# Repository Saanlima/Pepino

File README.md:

# Pepino
**For further information see the Pepino [Wiki](http://www.saanlima.com/pepino/index.php?title=Welcome_to_Pepino).**

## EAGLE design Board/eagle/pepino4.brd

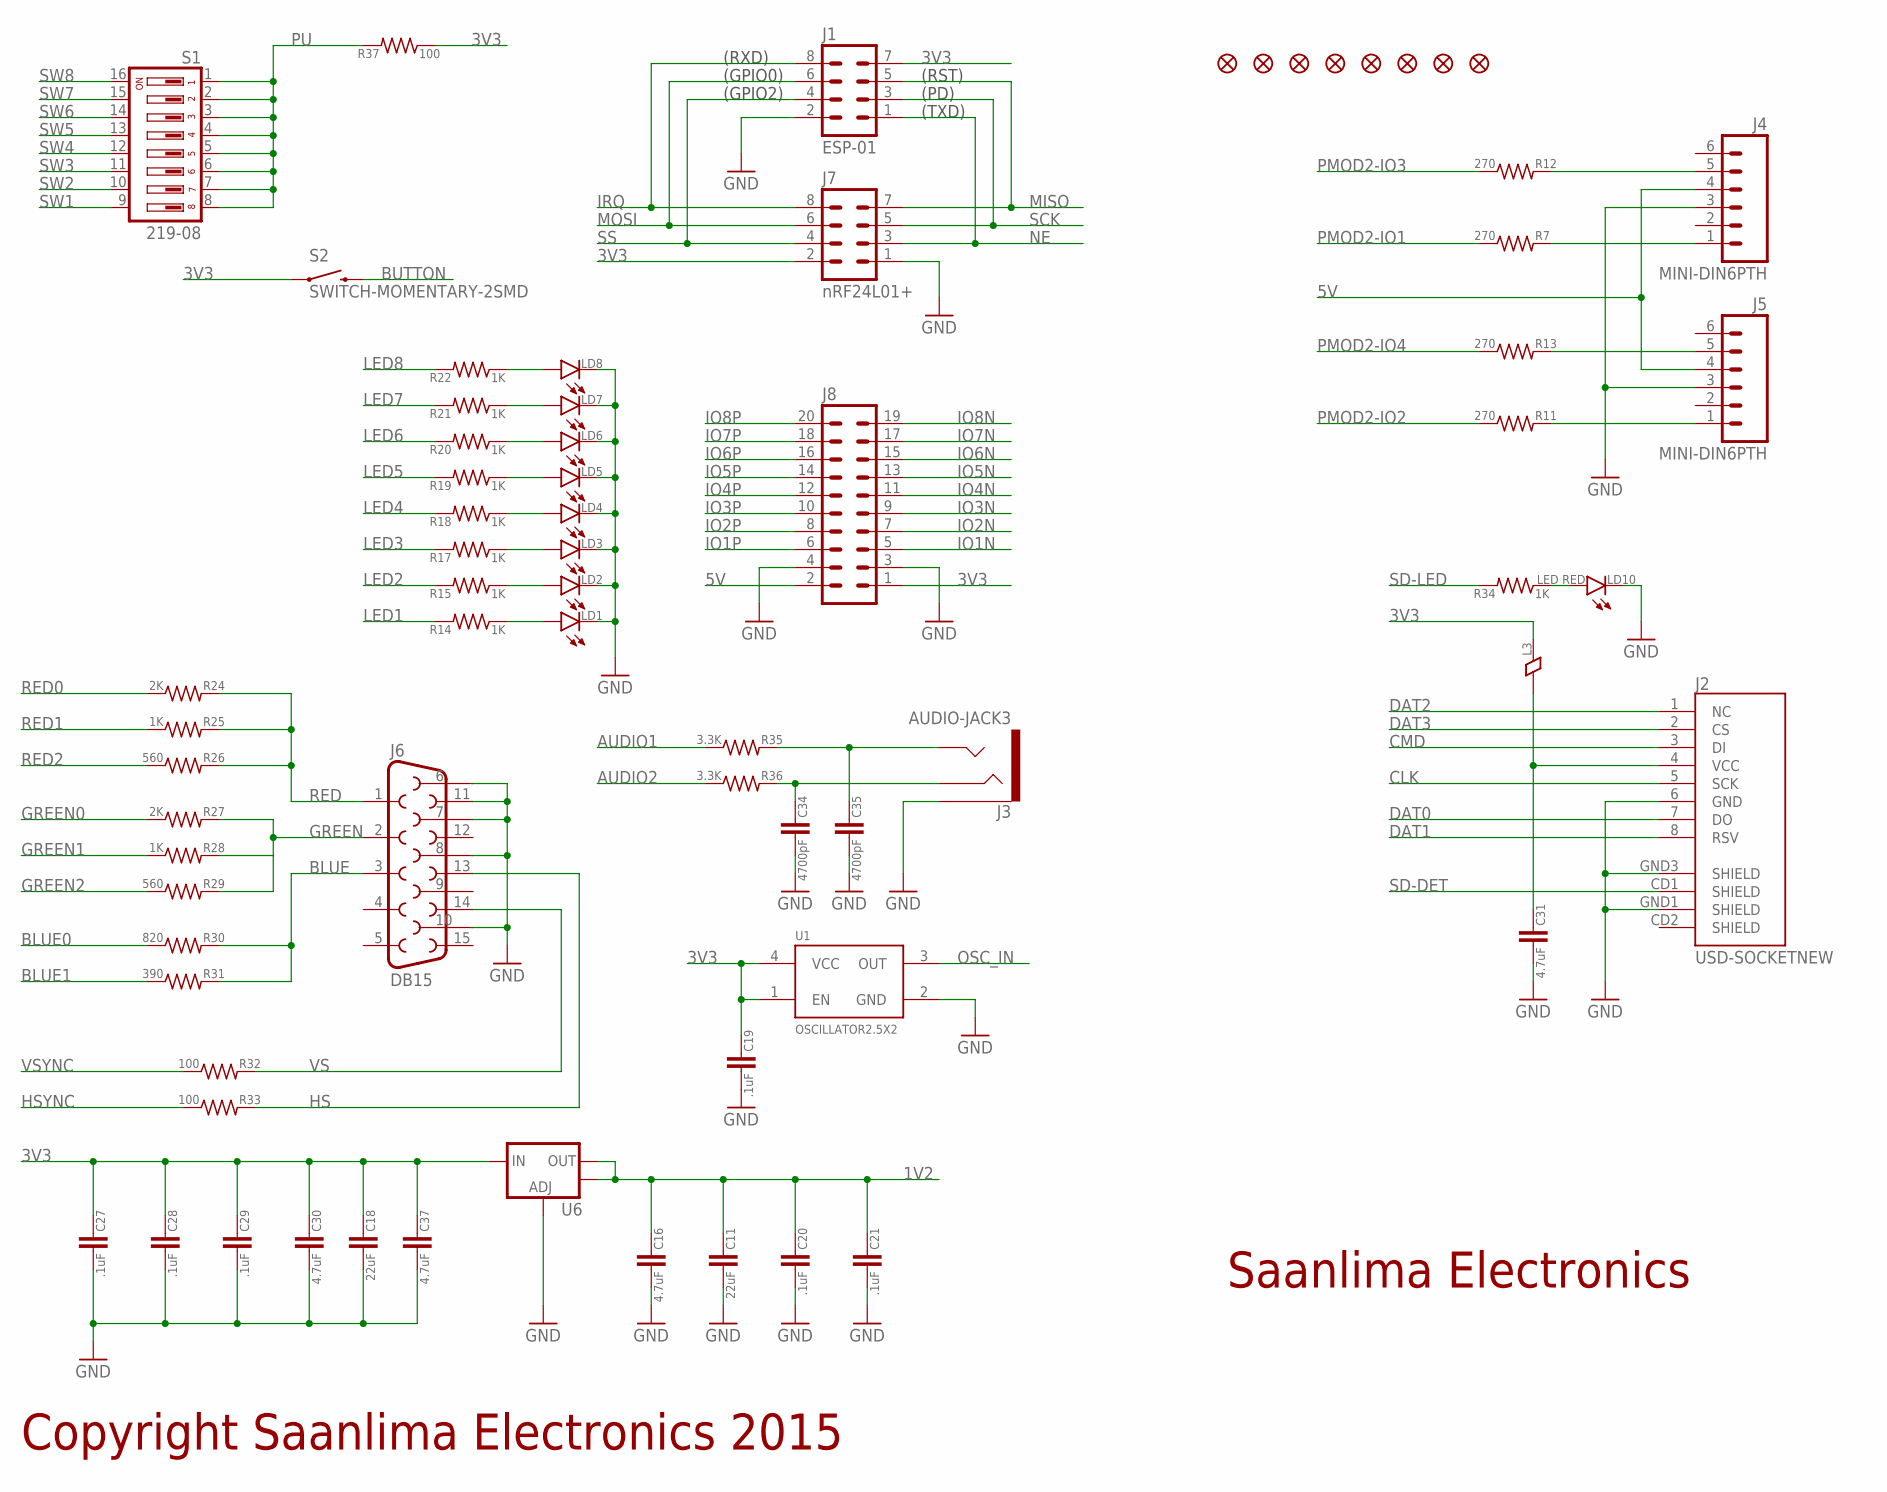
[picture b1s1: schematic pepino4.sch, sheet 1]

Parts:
C11, C18: 22uF; 0805
C16, C30, C31, C37: 4.7uF; 0402
C19, C20, C21, C27, C28, C29: .1uF; 0402
C34, C35: 4700pF; 0402
J1: ESP-01; MA04-2
J2: USD-SOCKETNEW; MICRO-SD-SOCKET-PP
J3: AUDIO-JACK3; AUDIO-JACK-3.5MM-3
J4, J5: MINI-DIN6PTH; MINI-DIN6
J6: DB15
J7: nRF24L01+; MA04-2
J8: MA10-2
JP1, JP2, JP3, JP4, JP5, JP6, JP7, JP8: FIDUCIAL1X2; FIDUCIAL-1X2
L3: FERRITE0402; 0402
LD1, LD2, LD3, LD4, LD5, LD6, LD7, LD8: LED0805; 0805_POL
LD10: LED RED; 0805_POL
R7, R11, R12, R13: 270; 0402
R14, R15, R17, R18, R19, R20, R21, R22, R25, R28, R34: 1K; 0402
R24, R27: 2K; 0402
R26, R29: 560; 0402
R30: 820; 0402
R31: 390; 0402
R32, R33, R37: 100; 0402
R35, R36: 3.3K; 0402
S1: 219-08; CTS-219-08
S2: SWITCH-MOMENTARY-2SMD; TACTILE_SWITCH_SMD
U1: OSCILLATOR2.5X2; CRYSTAL-OSC-SMD-2.5X2
U6: V_REG_LM1117SOT223; SOT223

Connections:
1V2: C11.1, C16.1, C20.1, C21.1, U6.2 (OUT), U6.4 (OUT); also elsewhere on the board
3V3: C18.1, C19.1, C27.1, C28.1, C29.1, C30.1, C37.1, J1.7, J7.2, J8.1, L3.2, R37.1, S2.1, U1.1 (EN), U1.4 (VCC), U6.3 (IN); also elsewhere on the board
5V: J4.4, J5.4, J8.2; also elsewhere on the board
AUDIO1: R35.1; also elsewhere on the board
AUDIO2: R36.1; also elsewhere on the board
BLUE: J6.3, R30.2, R31.2
BLUE0: R30.1; also elsewhere on the board
BLUE1: R31.1; also elsewhere on the board
BUTTON: S2.3 (2); also elsewhere on the board
CLK: J2.5 (SCK); also elsewhere on the board
CMD: J2.3 (DI); also elsewhere on the board
DAT0: J2.7 (DO); also elsewhere on the board
DAT1: J2.8 (RSV); also elsewhere on the board
DAT2: J2.1 (NC); also elsewhere on the board
DAT3: J2.2 (CS); also elsewhere on the board
GND: C11.2, C16.2, C18.2, C19.2, C20.2, C21.2, C27.2, C28.2, C29.2, C30.2, C31.2, C34.2, C35.2, C37.2, J1.2, J2.6 (GND), J2.GND1 (SHIELD), J2.GND3 (SHIELD), J3.SLEEVE, J4.3, J5.3, J6.6, J6.7, J6.8, J6.10, J6.11, J7.1, J8.3, J8.4, LD1.- (C), LD2.- (C), LD3.- (C), LD4.- (C), LD5.- (C), LD6.- (C), LD7.- (C), LD8.- (C), LD10.- (C), U1.2 (GND), U6.1 (ADJ); also elsewhere on the board
GREEN: J6.2, R27.2, R28.2, R29.2
GREEN0: R27.1; also elsewhere on the board
GREEN1: R28.1; also elsewhere on the board
GREEN2: R29.1; also elsewhere on the board
HS: J6.13, R33.2
HSYNC: R33.1; also elsewhere on the board
IO1N: J8.5; also elsewhere on the board
IO1P: J8.6; also elsewhere on the board
IO2N: J8.7; also elsewhere on the board
IO2P: J8.8; also elsewhere on the board
IO3N: J8.9; also elsewhere on the board
IO3P: J8.10; also elsewhere on the board
IO4N: J8.11; also elsewhere on the board
IO4P: J8.12; also elsewhere on the board
IO5N: J8.13; also elsewhere on the board
IO5P: J8.14; also elsewhere on the board
IO6N: J8.15; also elsewhere on the board
IO6P: J8.16; also elsewhere on the board
IO7N: J8.17; also elsewhere on the board
IO7P: J8.18; also elsewhere on the board
IO8N: J8.19; also elsewhere on the board
IO8P: J8.20; also elsewhere on the board
IRQ: J1.8, J7.8; also elsewhere on the board
LED1: R14.2; also elsewhere on the board
LED2: R15.2; also elsewhere on the board
LED3: R17.2; also elsewhere on the board
LED4: R18.2; also elsewhere on the board
LED5: R19.2; also elsewhere on the board
LED6: R20.2; also elsewhere on the board
LED7: R21.2; also elsewhere on the board
LED8: R22.2; also elsewhere on the board
MISO: J1.5, J7.7; also elsewhere on the board
MOSI: J1.6, J7.6; also elsewhere on the board
unnamed: J4.1, R7.2
unnamed: J5.1, R11.2
unnamed: J4.5, R12.2
unnamed: C31.1, J2.4 (VCC), L3.1
unnamed: J5.5, R13.2
unnamed: LD1.+ (A), R14.1
unnamed: LD7.+ (A), R21.1
unnamed: LD2.+ (A), R15.1
unnamed: LD3.+ (A), R17.1
unnamed: LD4.+ (A), R18.1
unnamed: LD5.+ (A), R19.1
unnamed: LD6.+ (A), R20.1
unnamed: LD8.+ (A), R22.1
unnamed: LD10.+ (A), R34.1
unnamed: C34.1, J3.RING, R36.2
unnamed: C35.1, J3.TIP, R35.2
NE: J1.1, J7.3; also elsewhere on the board
OSC_IN: U1.3 (OUT); also elsewhere on the board
PMOD2-IO1: R7.1; also elsewhere on the board
PMOD2-IO2: R11.1; also elsewhere on the board
PMOD2-IO3: R12.1; also elsewhere on the board
PMOD2-IO4: R13.1; also elsewhere on the board
PU: R37.2, S1.1, S1.2, S1.3, S1.4, S1.5, S1.6, S1.7, S1.8
RED: J6.1, R24.2, R25.2, R26.2
RED0: R24.1; also elsewhere on the board
RED1: R25.1; also elsewhere on the board
RED2: R26.1; also elsewhere on the board
SCK: J1.3, J7.5; also elsewhere on the board
SD-DET: J2.CD1 (SHIELD); also elsewhere on the board
SD-LED: R34.2; also elsewhere on the board
SS: J1.4, J7.4; also elsewhere on the board
SW1: S1.9; also elsewhere on the board
SW2: S1.10; also elsewhere on the board
SW3: S1.11; also elsewhere on the board
SW4: S1.12; also elsewhere on the board
SW5: S1.13; also elsewhere on the board
SW6: S1.14; also elsewhere on the board
SW7: S1.15; also elsewhere on the board
SW8: S1.16; also elsewhere on the board
VS: J6.14, R32.2
VSYNC: R32.1; also elsewhere on the board

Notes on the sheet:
(RST)
(PD)
(TXD)
(RXD)
(GPIO0)
(GPIO2)
Saanlima Electronics
Copyright Saanlima Electronics 2015

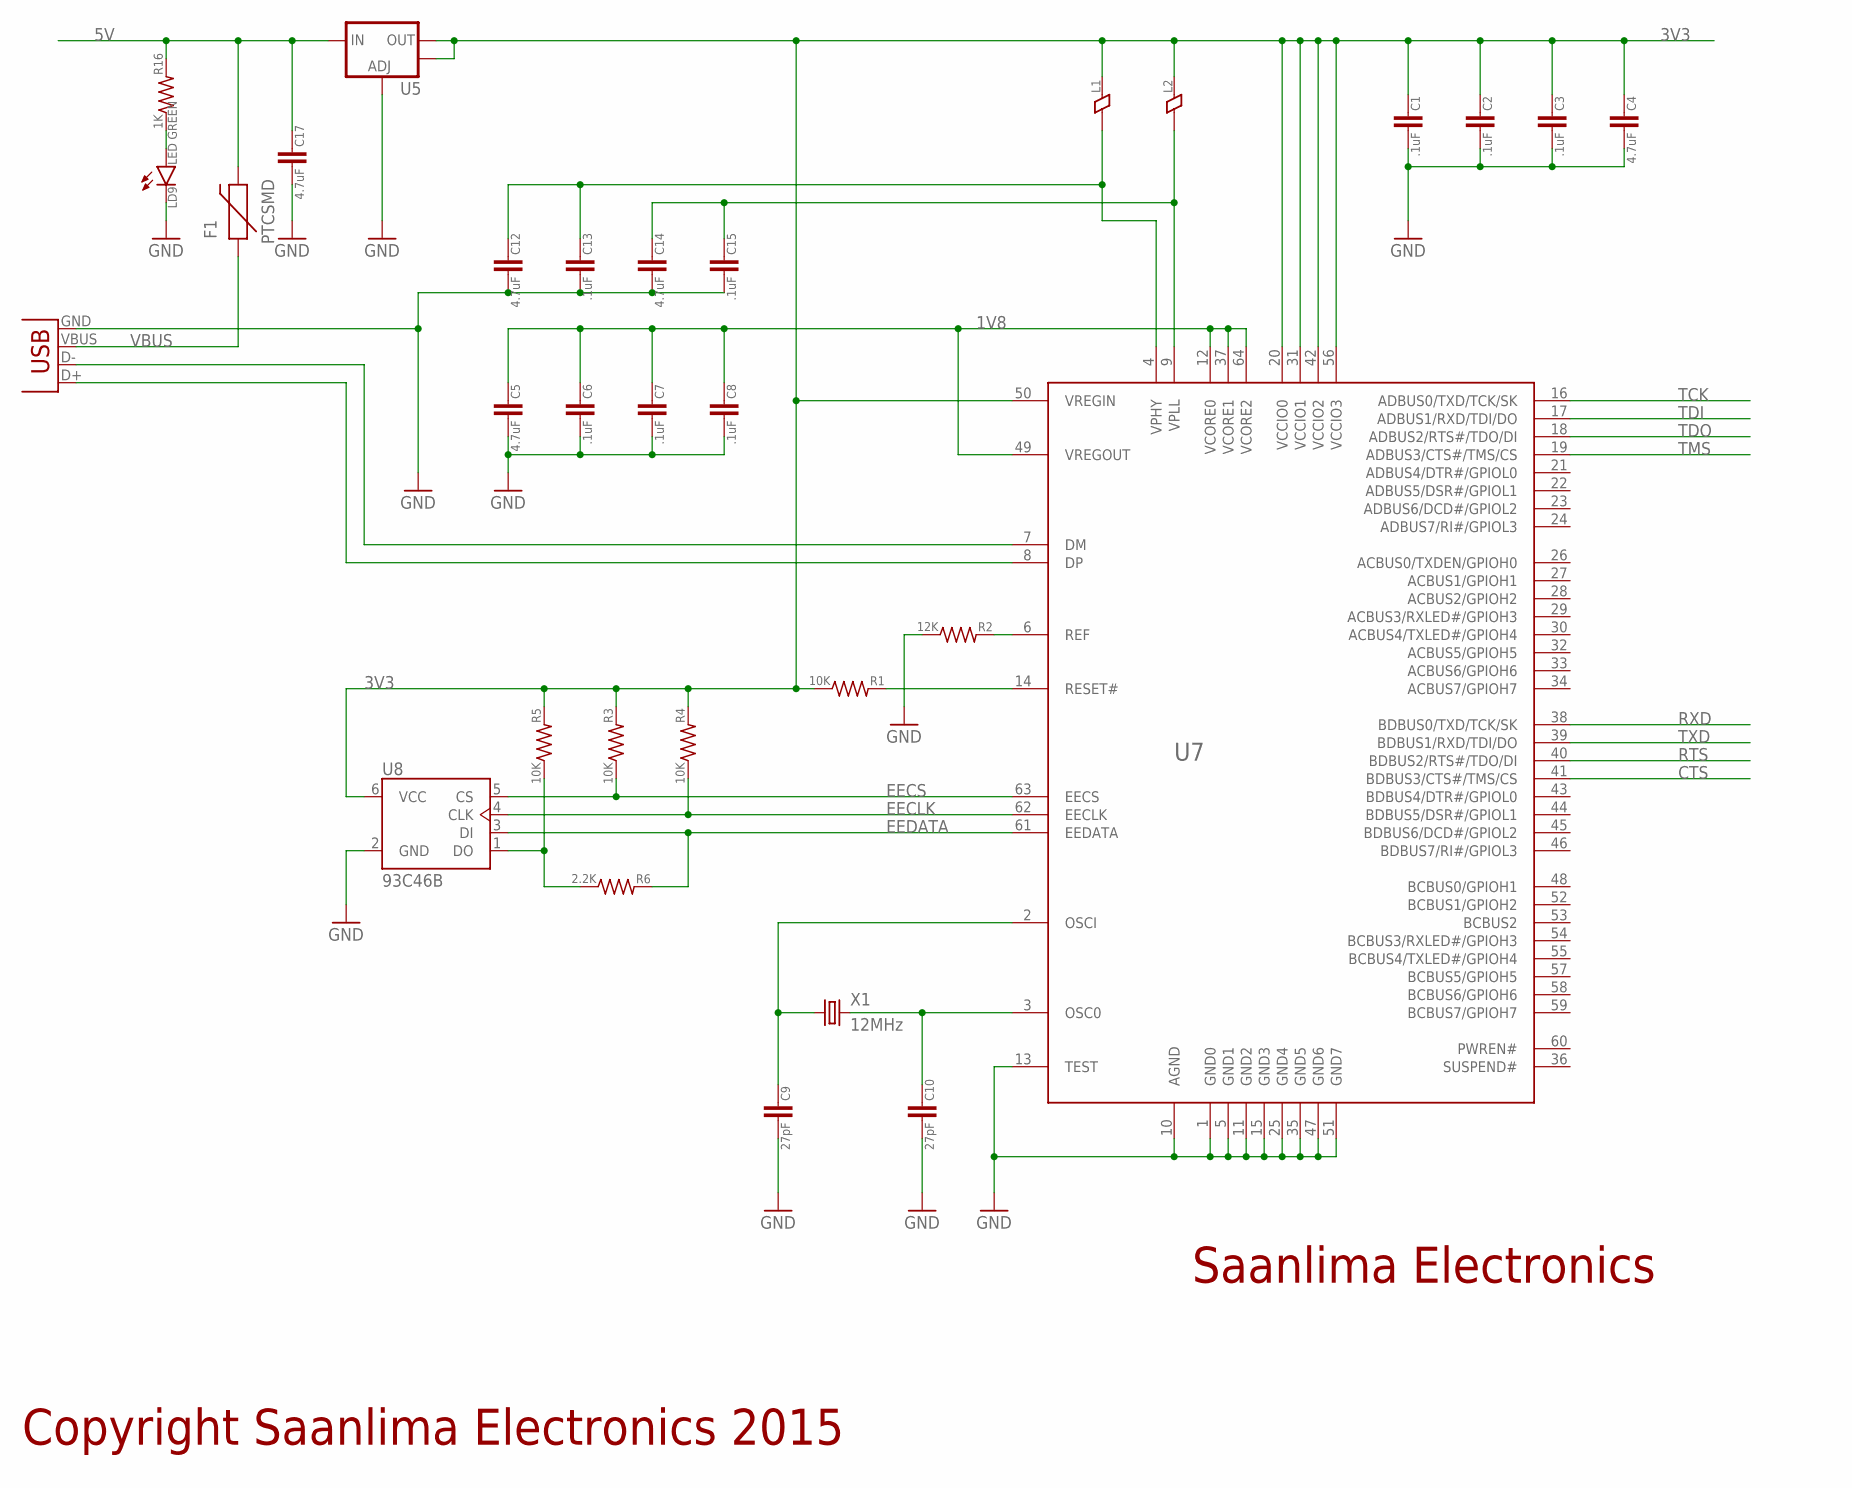
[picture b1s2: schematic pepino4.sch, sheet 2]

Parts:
C1, C2, C3, C6, C7, C8, C13, C15: .1uF; 0402
C4, C5, C12, C14: 4.7uF; 0402
C9, C10: 27pF; 0402
C17: 4.7uF; 0603
F1: PTCSMD; PTC-1206
J9: USBSMD; USB-MINIB
L1, L2: FERRITE0402; 0402
LD9: LED GREEN; 0805_POL
R1, R3, R4, R5: 10K; 0402
R2: 12K; 0402
R6: 2.2K; 0402
R16: 1K; 0402
U5: V_REG_LM1117SOT223; SOT223
U7: DP-EAGLELIBRARY_FT2232H; DP-EAGLELIBRARY_LQFP64
U8: 93C46B; SOT23-6
X1: 12MHz; CRYSTAL3.2X2.5MM

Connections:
1V8: C5.1, C6.1, C7.1, C8.1, U7.12 (VCORE0), U7.37 (VCORE1), U7.49 (VREGOUT), U7.64 (VCORE2)
3V3: C1.1, C2.1, C3.1, C4.1, L1.2, L2.2, R1.1, R3.2, R4.2, R5.2, U5.2 (OUT), U5.4 (OUT), U7.20 (VCCIO0), U7.31 (VCCIO1), U7.42 (VCCIO2), U7.50 (VREGIN), U7.56 (VCCIO3), U8.6 (VCC); also elsewhere on the board
5V: C17.1, F1.2, R16.2, U5.3 (IN); also elsewhere on the board
CTS: U7.41 (BDBUS3/CTS#/TMS/CS); also elsewhere on the board
EECLK: R4.1, U7.62 (EECLK), U8.4 (CLK)
EECS: R3.1, U7.63 (EECS), U8.5 (CS)
EEDATA: R6.2, U7.61 (EEDATA), U8.3 (DI)
GND: C1.2, C2.2, C3.2, C4.2, C5.2, C6.2, C7.2, C8.2, C9.2, C10.2, C12.2, C13.2, C14.2, C15.2, C17.2, J9.GND, LD9.- (C), R2.1, U5.1 (ADJ), U7.1 (GND0), U7.5 (GND1), U7.10 (AGND), U7.11 (GND2), U7.13 (TEST), U7.15 (GND3), U7.25 (GND4), U7.35 (GND5), U7.47 (GND6), U7.51 (GND7), U8.2 (GND); also elsewhere on the board
unnamed: C9.1, U7.2 (OSCI), X1.1
unnamed: C10.1, U7.3 (OSC0), X1.3 (2)
unnamed: LD9.+ (A), R16.1
unnamed: J9.D-, U7.7 (DM)
unnamed: J9.D+, U7.8 (DP)
unnamed: C14.1, C15.1, L2.1, U7.9 (VPLL)
unnamed: R1.2, U7.14 (RESET#)
unnamed: R2.2, U7.6 (REF)
unnamed: C12.1, C13.1, L1.1, U7.4 (VPHY)
unnamed: R5.1, R6.1, U8.1 (DO)
RTS: U7.40 (BDBUS2/RTS#/TDO/DI); also elsewhere on the board
RXD: U7.38 (BDBUS0/TXD/TCK/SK); also elsewhere on the board
TCK: U7.16 (ADBUS0/TXD/TCK/SK); also elsewhere on the board
TDI: U7.17 (ADBUS1/RXD/TDI/DO); also elsewhere on the board
TDO: U7.18 (ADBUS2/RTS#/TDO/DI); also elsewhere on the board
TMS: U7.19 (ADBUS3/CTS#/TMS/CS); also elsewhere on the board
TXD: U7.39 (BDBUS1/RXD/TDI/DO); also elsewhere on the board
VBUS: F1.1, J9.VBUS

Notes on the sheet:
Copyright Saanlima Electronics 2015
Saanlima Electronics

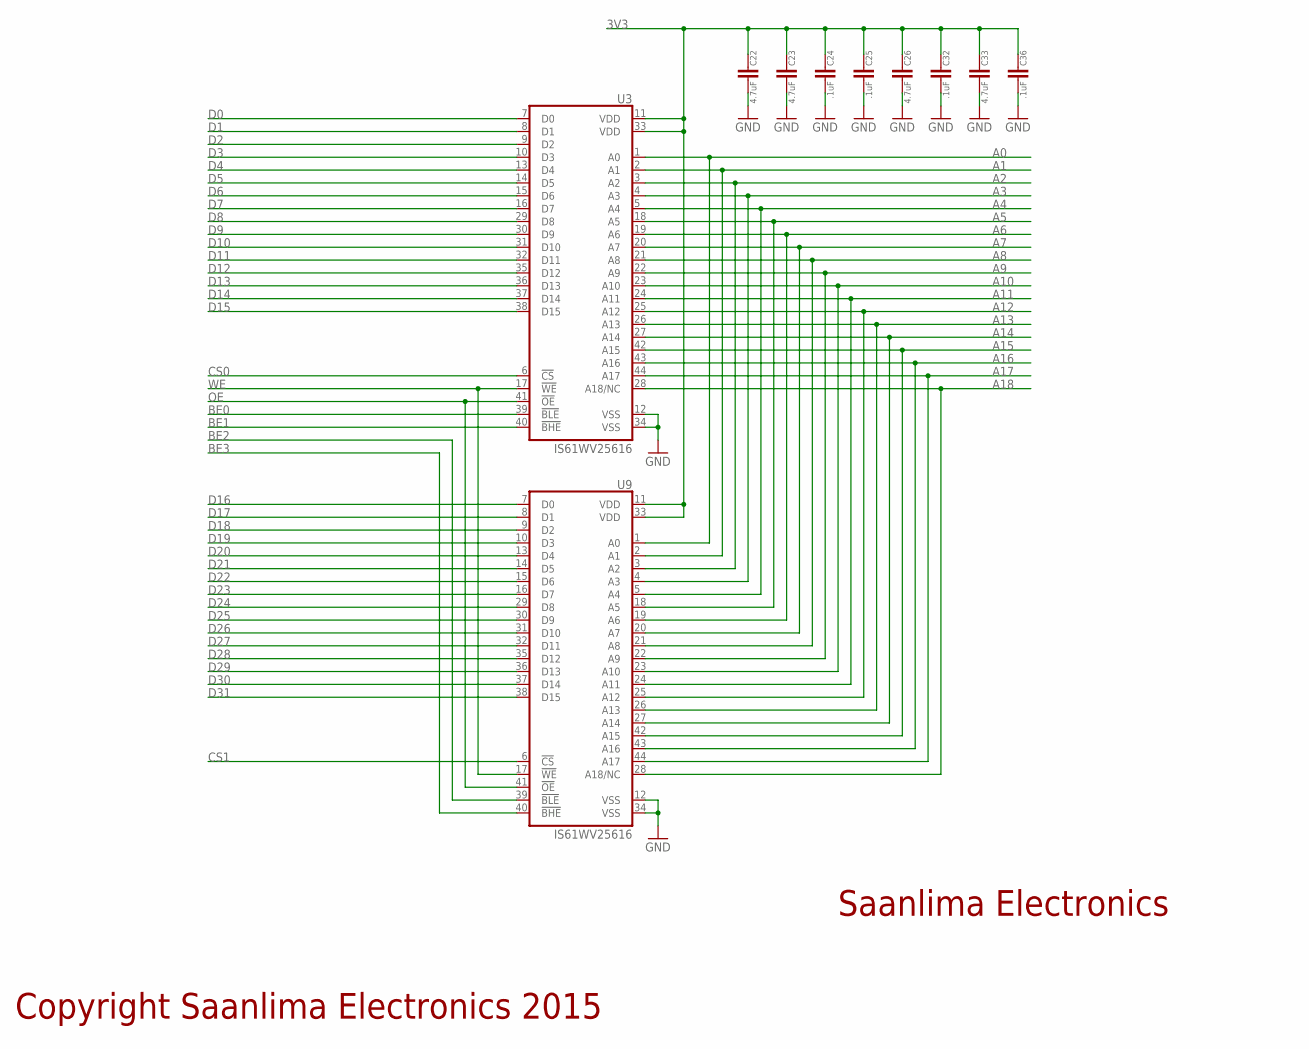
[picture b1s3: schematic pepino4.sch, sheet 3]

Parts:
C22, C23, C26, C33: 4.7uF; 0402
C24, C25, C32, C36: .1uF; 0402
U3, U9: IS61WV25616; TSOP44-II

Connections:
3V3: C22.1, C23.1, C24.1, C25.1, C26.1, C32.1, C33.1, C36.1, U3.11 (VDD), U3.33 (VDD), U9.11 (VDD), U9.33 (VDD); also elsewhere on the board
A0: U3.1 (A0), U9.1 (A0); also elsewhere on the board
A1: U3.2 (A1), U9.2 (A1); also elsewhere on the board
A2: U3.3 (A2), U9.3 (A2); also elsewhere on the board
A3: U3.4 (A3), U9.4 (A3); also elsewhere on the board
A4: U3.5 (A4), U9.5 (A4); also elsewhere on the board
A5: U3.18 (A5), U9.18 (A5); also elsewhere on the board
A6: U3.19 (A6), U9.19 (A6); also elsewhere on the board
A7: U3.20 (A7), U9.20 (A7); also elsewhere on the board
A8: U3.21 (A8), U9.21 (A8); also elsewhere on the board
A9: U3.22 (A9), U9.22 (A9); also elsewhere on the board
A10: U3.23 (A10), U9.23 (A10); also elsewhere on the board
A11: U3.24 (A11), U9.24 (A11); also elsewhere on the board
A12: U3.25 (A12), U9.25 (A12); also elsewhere on the board
A13: U3.26 (A13), U9.26 (A13); also elsewhere on the board
A14: U3.27 (A14), U9.27 (A14); also elsewhere on the board
A15: U3.42 (A15), U9.42 (A15); also elsewhere on the board
A16: U3.43 (A16), U9.43 (A16); also elsewhere on the board
A17: U3.44 (A17), U9.44 (A17); also elsewhere on the board
A18: U3.28 (A18/NC), U9.28 (A18/NC); also elsewhere on the board
BE0: U3.39 (!BLE); also elsewhere on the board
BE1: U3.40 (!BHE); also elsewhere on the board
BE2: U9.39 (!BLE); also elsewhere on the board
BE3: U9.40 (!BHE); also elsewhere on the board
CS0: U3.6 (!CS); also elsewhere on the board
CS1: U9.6 (!CS); also elsewhere on the board
D0: U3.7 (D0); also elsewhere on the board
D1: U3.8 (D1); also elsewhere on the board
D2: U3.9 (D2); also elsewhere on the board
D3: U3.10 (D3); also elsewhere on the board
D4: U3.13 (D4); also elsewhere on the board
D5: U3.14 (D5); also elsewhere on the board
D6: U3.15 (D6); also elsewhere on the board
D7: U3.16 (D7); also elsewhere on the board
D8: U3.29 (D8); also elsewhere on the board
D9: U3.30 (D9); also elsewhere on the board
D10: U3.31 (D10); also elsewhere on the board
D11: U3.32 (D11); also elsewhere on the board
D12: U3.35 (D12); also elsewhere on the board
D13: U3.36 (D13); also elsewhere on the board
D14: U3.37 (D14); also elsewhere on the board
D15: U3.38 (D15); also elsewhere on the board
D16: U9.7 (D0); also elsewhere on the board
D17: U9.8 (D1); also elsewhere on the board
D18: U9.9 (D2); also elsewhere on the board
D19: U9.10 (D3); also elsewhere on the board
D20: U9.13 (D4); also elsewhere on the board
D21: U9.14 (D5); also elsewhere on the board
D22: U9.15 (D6); also elsewhere on the board
D23: U9.16 (D7); also elsewhere on the board
D24: U9.29 (D8); also elsewhere on the board
D25: U9.30 (D9); also elsewhere on the board
D26: U9.31 (D10); also elsewhere on the board
D27: U9.32 (D11); also elsewhere on the board
D28: U9.35 (D12); also elsewhere on the board
D29: U9.36 (D13); also elsewhere on the board
D30: U9.37 (D14); also elsewhere on the board
D31: U9.38 (D15); also elsewhere on the board
GND: C22.2, C23.2, C24.2, C25.2, C26.2, C32.2, C33.2, C36.2, U3.12 (VSS), U3.34 (VSS), U9.12 (VSS), U9.34 (VSS); also elsewhere on the board
OE: U3.41 (!OE), U9.41 (!OE); also elsewhere on the board
WE: U3.17 (!WE), U9.17 (!WE); also elsewhere on the board

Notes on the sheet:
Copyright Saanlima Electronics 2015
Saanlima Electronics

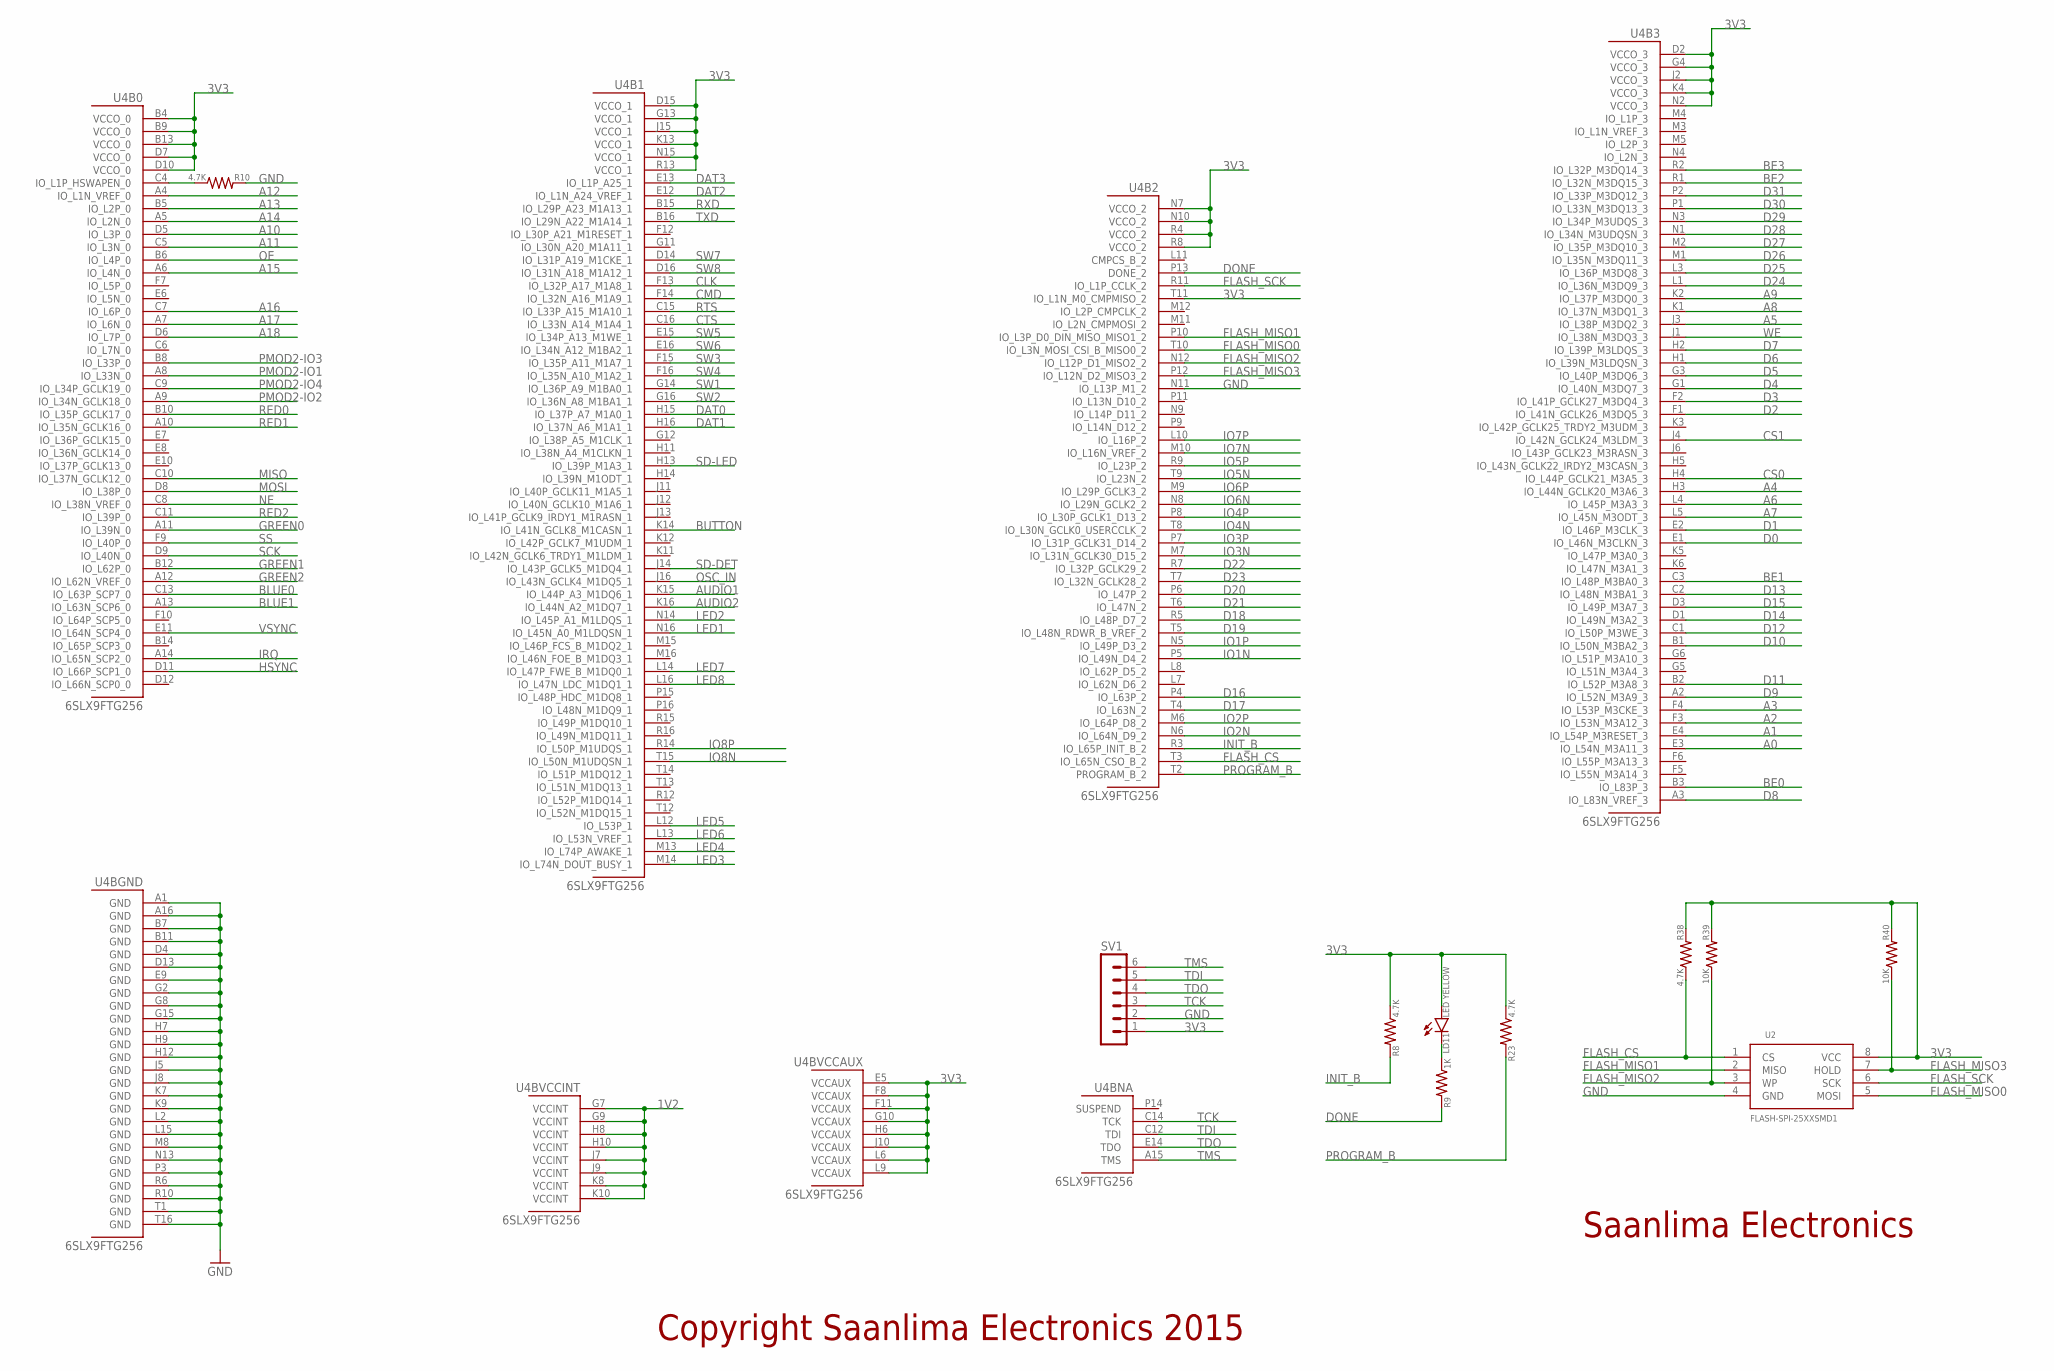
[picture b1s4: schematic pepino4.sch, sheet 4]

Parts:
LD11: LED YELLOW; 0805_POL
R8, R10, R23, R38: 4.7K; 0402
R9: 1K; 0402
R39, R40: 10K; 0402
SV1: MA06-1
U2: FLASH-SPI-25XXSMD1; SO08-EIAJ
U4: 6SLX9FTG256; FT256

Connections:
1V2: U4.G7 (VCCINT), U4.G9 (VCCINT), U4.H8 (VCCINT), U4.H10 (VCCINT), U4.J7 (VCCINT), U4.J9 (VCCINT), U4.K8 (VCCINT), U4.K10 (VCCINT); also elsewhere on the board
3V3: LD11.+ (A), R8.1, R23.1, R38.2, R39.2, R40.2, SV1.1, U2.8 (VCC), U4.B4 (VCCO_0), U4.B9 (VCCO_0), U4.B13 (VCCO_0), U4.D2 (VCCO_3), U4.D7 (VCCO_0), U4.D10 (VCCO_0), U4.D15 (VCCO_1), U4.E5 (VCCAUX), U4.F8 (VCCAUX), U4.F11 (VCCAUX), U4.G4 (VCCO_3), U4.G10 (VCCAUX), U4.G13 (VCCO_1), U4.H6 (VCCAUX), U4.J2 (VCCO_3), U4.J10 (VCCAUX), U4.J15 (VCCO_1), U4.K4 (VCCO_3), U4.K13 (VCCO_1), U4.L6 (VCCAUX), U4.L9 (VCCAUX), U4.N2 (VCCO_3), U4.N7 (VCCO_2), U4.N10 (VCCO_2), U4.N15 (VCCO_1), U4.R4 (VCCO_2), U4.R8 (VCCO_2), U4.R13 (VCCO_1), U4.T11 (IO_L1N_M0_CMPMISO_2); also elsewhere on the board
A0: U4.E3 (IO_L54N_M3A11_3); also elsewhere on the board
A1: U4.E4 (IO_L54P_M3RESET_3); also elsewhere on the board
A2: U4.F3 (IO_L53N_M3A12_3); also elsewhere on the board
A3: U4.F4 (IO_L53P_M3CKE_3); also elsewhere on the board
A4: U4.H3 (IO_L44N_GCLK20_M3A6_3); also elsewhere on the board
A5: U4.J3 (IO_L38P_M3DQ2_3); also elsewhere on the board
A6: U4.L4 (IO_L45P_M3A3_3); also elsewhere on the board
A7: U4.L5 (IO_L45N_M3ODT_3); also elsewhere on the board
A8: U4.K1 (IO_L37N_M3DQ1_3); also elsewhere on the board
A9: U4.K2 (IO_L37P_M3DQ0_3); also elsewhere on the board
A10: U4.D5 (IO_L3P_0); also elsewhere on the board
A11: U4.C5 (IO_L3N_0); also elsewhere on the board
A12: U4.A4 (IO_L1N_VREF_0); also elsewhere on the board
A13: U4.B5 (IO_L2P_0); also elsewhere on the board
A14: U4.A5 (IO_L2N_0); also elsewhere on the board
A15: U4.A6 (IO_L4N_0); also elsewhere on the board
A16: U4.C7 (IO_L6P_0); also elsewhere on the board
A17: U4.A7 (IO_L6N_0); also elsewhere on the board
A18: U4.D6 (IO_L7P_0); also elsewhere on the board
AUDIO1: U4.K15 (IO_L44P_A3_M1DQ6_1); also elsewhere on the board
AUDIO2: U4.K16 (IO_L44N_A2_M1DQ7_1); also elsewhere on the board
BE0: U4.B3 (IO_L83P_3); also elsewhere on the board
BE1: U4.C3 (IO_L48P_M3BA0_3); also elsewhere on the board
BE2: U4.R1 (IO_L32N_M3DQ15_3); also elsewhere on the board
BE3: U4.R2 (IO_L32P_M3DQ14_3); also elsewhere on the board
BLUE0: U4.C13 (IO_L63P_SCP7_0); also elsewhere on the board
BLUE1: U4.A13 (IO_L63N_SCP6_0); also elsewhere on the board
BUTTON: U4.K14 (IO_L41N_GCLK8_M1CASN_1); also elsewhere on the board
CLK: U4.F13 (IO_L32P_A17_M1A8_1); also elsewhere on the board
CMD: U4.F14 (IO_L32N_A16_M1A9_1); also elsewhere on the board
CS0: U4.H4 (IO_L44P_GCLK21_M3A5_3); also elsewhere on the board
CS1: U4.J4 (IO_L42N_GCLK24_M3LDM_3); also elsewhere on the board
CTS: U4.C16 (IO_L33N_A14_M1A4_1); also elsewhere on the board
D0: U4.E1 (IO_L46N_M3CLKN_3); also elsewhere on the board
D1: U4.E2 (IO_L46P_M3CLK_3); also elsewhere on the board
D2: U4.F1 (IO_L41N_GCLK26_M3DQ5_3); also elsewhere on the board
D3: U4.F2 (IO_L41P_GCLK27_M3DQ4_3); also elsewhere on the board
D4: U4.G1 (IO_L40N_M3DQ7_3); also elsewhere on the board
D5: U4.G3 (IO_L40P_M3DQ6_3); also elsewhere on the board
D6: U4.H1 (IO_L39N_M3LDQSN_3); also elsewhere on the board
D7: U4.H2 (IO_L39P_M3LDQS_3); also elsewhere on the board
D8: U4.A3 (IO_L83N_VREF_3); also elsewhere on the board
D9: U4.A2 (IO_L52N_M3A9_3); also elsewhere on the board
D10: U4.B1 (IO_L50N_M3BA2_3); also elsewhere on the board
D11: U4.B2 (IO_L52P_M3A8_3); also elsewhere on the board
D12: U4.C1 (IO_L50P_M3WE_3); also elsewhere on the board
D13: U4.C2 (IO_L48N_M3BA1_3); also elsewhere on the board
D14: U4.D1 (IO_L49N_M3A2_3); also elsewhere on the board
D15: U4.D3 (IO_L49P_M3A7_3); also elsewhere on the board
D16: U4.P4 (IO_L63P_2); also elsewhere on the board
D17: U4.T4 (IO_L63N_2); also elsewhere on the board
D18: U4.R5 (IO_L48P_D7_2); also elsewhere on the board
D19: U4.T5 (IO_L48N_RDWR_B_VREF_2); also elsewhere on the board
D20: U4.P6 (IO_L47P_2); also elsewhere on the board
D21: U4.T6 (IO_L47N_2); also elsewhere on the board
D22: U4.R7 (IO_L32P_GCLK29_2); also elsewhere on the board
D23: U4.T7 (IO_L32N_GCLK28_2); also elsewhere on the board
D24: U4.L1 (IO_L36N_M3DQ9_3); also elsewhere on the board
D25: U4.L3 (IO_L36P_M3DQ8_3); also elsewhere on the board
D26: U4.M1 (IO_L35N_M3DQ11_3); also elsewhere on the board
D27: U4.M2 (IO_L35P_M3DQ10_3); also elsewhere on the board
D28: U4.N1 (IO_L34N_M3UDQSN_3); also elsewhere on the board
D29: U4.N3 (IO_L34P_M3UDQS_3); also elsewhere on the board
D30: U4.P1 (IO_L33N_M3DQ13_3); also elsewhere on the board
D31: U4.P2 (IO_L33P_M3DQ12_3); also elsewhere on the board
DAT0: U4.H15 (IO_L37P_A7_M1A0_1); also elsewhere on the board
DAT1: U4.H16 (IO_L37N_A6_M1A1_1); also elsewhere on the board
DAT2: U4.E12 (IO_L1N_A24_VREF_1); also elsewhere on the board
DAT3: U4.E13 (IO_L1P_A25_1); also elsewhere on the board
DONE: R9.2, U4.P13 (DONE_2)
FLASH_CS: R38.1, U2.1 (CS), U4.T3 (IO_L65N_CSO_B_2)
FLASH_MISO0: U2.5 (MOSI), U4.T10 (IO_L3N_MOSI_CSI_B_MISO0_2)
FLASH_MISO1: U2.2 (MISO), U4.P10 (IO_L3P_D0_DIN_MISO_MISO1_2)
FLASH_MISO2: R39.1, U2.3 (WP), U4.N12 (IO_L12P_D1_MISO2_2)
FLASH_MISO3: R40.1, U2.7 (HOLD), U4.P12 (IO_L12N_D2_MISO3_2)
FLASH_SCK: U2.6 (SCK), U4.R11 (IO_L1P_CCLK_2)
GND: R10.2, SV1.2, U2.4 (GND), U4.A1 (GND), U4.A16 (GND), U4.B7 (GND), U4.B11 (GND), U4.D4 (GND), U4.D13 (GND), U4.E9 (GND), U4.G2 (GND), U4.G8 (GND), U4.G15 (GND), U4.H7 (GND), U4.H9 (GND), U4.H12 (GND), U4.J5 (GND), U4.J8 (GND), U4.K7 (GND), U4.K9 (GND), U4.L2 (GND), U4.L15 (GND), U4.M8 (GND), U4.N11 (IO_L13P_M1_2), U4.N13 (GND), U4.P3 (GND), U4.R6 (GND), U4.R10 (GND), U4.T1 (GND), U4.T16 (GND); also elsewhere on the board
GREEN0: U4.A11 (IO_L39N_0); also elsewhere on the board
GREEN1: U4.B12 (IO_L62P_0); also elsewhere on the board
GREEN2: U4.A12 (IO_L62N_VREF_0); also elsewhere on the board
HSYNC: U4.D11 (IO_L66P_SCP1_0); also elsewhere on the board
INIT_B: R8.2, U4.R3 (IO_L65P_INIT_B_2)
IO1N: U4.P5 (IO_L49N_D4_2); also elsewhere on the board
IO1P: U4.N5 (IO_L49P_D3_2); also elsewhere on the board
IO2N: U4.N6 (IO_L64N_D9_2); also elsewhere on the board
IO2P: U4.M6 (IO_L64P_D8_2); also elsewhere on the board
IO3N: U4.M7 (IO_L31N_GCLK30_D15_2); also elsewhere on the board
IO3P: U4.P7 (IO_L31P_GCLK31_D14_2); also elsewhere on the board
IO4N: U4.T8 (IO_L30N_GCLK0_USERCCLK_2); also elsewhere on the board
IO4P: U4.P8 (IO_L30P_GCLK1_D13_2); also elsewhere on the board
IO5N: U4.T9 (IO_L23N_2); also elsewhere on the board
IO5P: U4.R9 (IO_L23P_2); also elsewhere on the board
IO6N: U4.N8 (IO_L29N_GCLK2_2); also elsewhere on the board
IO6P: U4.M9 (IO_L29P_GCLK3_2); also elsewhere on the board
IO7N: U4.M10 (IO_L16N_VREF_2); also elsewhere on the board
IO7P: U4.L10 (IO_L16P_2); also elsewhere on the board
IO8N: U4.T15 (IO_L50N_M1UDQSN_1); also elsewhere on the board
IO8P: U4.R14 (IO_L50P_M1UDQS_1); also elsewhere on the board
IRQ: U4.A14 (IO_L65N_SCP2_0); also elsewhere on the board
LED1: U4.N16 (IO_L45N_A0_M1LDQSN_1); also elsewhere on the board
LED2: U4.N14 (IO_L45P_A1_M1LDQS_1); also elsewhere on the board
LED3: U4.M14 (IO_L74N_DOUT_BUSY_1); also elsewhere on the board
LED4: U4.M13 (IO_L74P_AWAKE_1); also elsewhere on the board
LED5: U4.L12 (IO_L53P_1); also elsewhere on the board
LED6: U4.L13 (IO_L53N_VREF_1); also elsewhere on the board
LED7: U4.L14 (IO_L47P_FWE_B_M1DQ0_1); also elsewhere on the board
LED8: U4.L16 (IO_L47N_LDC_M1DQ1_1); also elsewhere on the board
MISO: U4.C10 (IO_L37N_GCLK12_0); also elsewhere on the board
MOSI: U4.D8 (IO_L38P_0); also elsewhere on the board
unnamed: LD11.- (C), R9.1
unnamed: R10.1, U4.C4 (IO_L1P_HSWAPEN_0)
NE: U4.C8 (IO_L38N_VREF_0); also elsewhere on the board
OE: U4.B6 (IO_L4P_0); also elsewhere on the board
OSC_IN: U4.J16 (IO_L43N_GCLK4_M1DQ5_1); also elsewhere on the board
PMOD2-IO1: U4.A8 (IO_L33N_0); also elsewhere on the board
PMOD2-IO2: U4.A9 (IO_L34N_GCLK18_0); also elsewhere on the board
PMOD2-IO3: U4.B8 (IO_L33P_0); also elsewhere on the board
PMOD2-IO4: U4.C9 (IO_L34P_GCLK19_0); also elsewhere on the board
PROGRAM_B: R23.2, U4.T2 (PROGRAM_B_2)
RED0: U4.B10 (IO_L35P_GCLK17_0); also elsewhere on the board
RED1: U4.A10 (IO_L35N_GCLK16_0); also elsewhere on the board
RED2: U4.C11 (IO_L39P_0); also elsewhere on the board
RTS: U4.C15 (IO_L33P_A15_M1A10_1); also elsewhere on the board
RXD: U4.B15 (IO_L29P_A23_M1A13_1); also elsewhere on the board
SCK: U4.D9 (IO_L40N_0); also elsewhere on the board
SD-DET: U4.J14 (IO_L43P_GCLK5_M1DQ4_1); also elsewhere on the board
SD-LED: U4.H13 (IO_L39P_M1A3_1); also elsewhere on the board
SS: U4.F9 (IO_L40P_0); also elsewhere on the board
SW1: U4.G14 (IO_L36P_A9_M1BA0_1); also elsewhere on the board
SW2: U4.G16 (IO_L36N_A8_M1BA1_1); also elsewhere on the board
SW3: U4.F15 (IO_L35P_A11_M1A7_1); also elsewhere on the board
SW4: U4.F16 (IO_L35N_A10_M1A2_1); also elsewhere on the board
SW5: U4.E15 (IO_L34P_A13_M1WE_1); also elsewhere on the board
SW6: U4.E16 (IO_L34N_A12_M1BA2_1); also elsewhere on the board
SW7: U4.D14 (IO_L31P_A19_M1CKE_1); also elsewhere on the board
SW8: U4.D16 (IO_L31N_A18_M1A12_1); also elsewhere on the board
TCK: SV1.3, U4.C14 (TCK); also elsewhere on the board
TDI: SV1.5, U4.C12 (TDI); also elsewhere on the board
TDO: SV1.4, U4.E14 (TDO); also elsewhere on the board
TMS: SV1.6, U4.A15 (TMS); also elsewhere on the board
TXD: U4.B16 (IO_L29N_A22_M1A14_1); also elsewhere on the board
VSYNC: U4.E11 (IO_L64N_SCP4_0); also elsewhere on the board
WE: U4.J1 (IO_L38N_M3DQ3_3); also elsewhere on the board

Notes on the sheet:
Copyright Saanlima Electronics 2015
Saanlima Electronics

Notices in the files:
Board/eagle/pepino4.brd:
Copyright 2015 Saanlima Electronics
parts and their libraries:
SparkFun-Connectors: Licensing: Creative Commons ShareAlike 4.0 International - https://creativecommons.org/licenses/by-sa/4.0
